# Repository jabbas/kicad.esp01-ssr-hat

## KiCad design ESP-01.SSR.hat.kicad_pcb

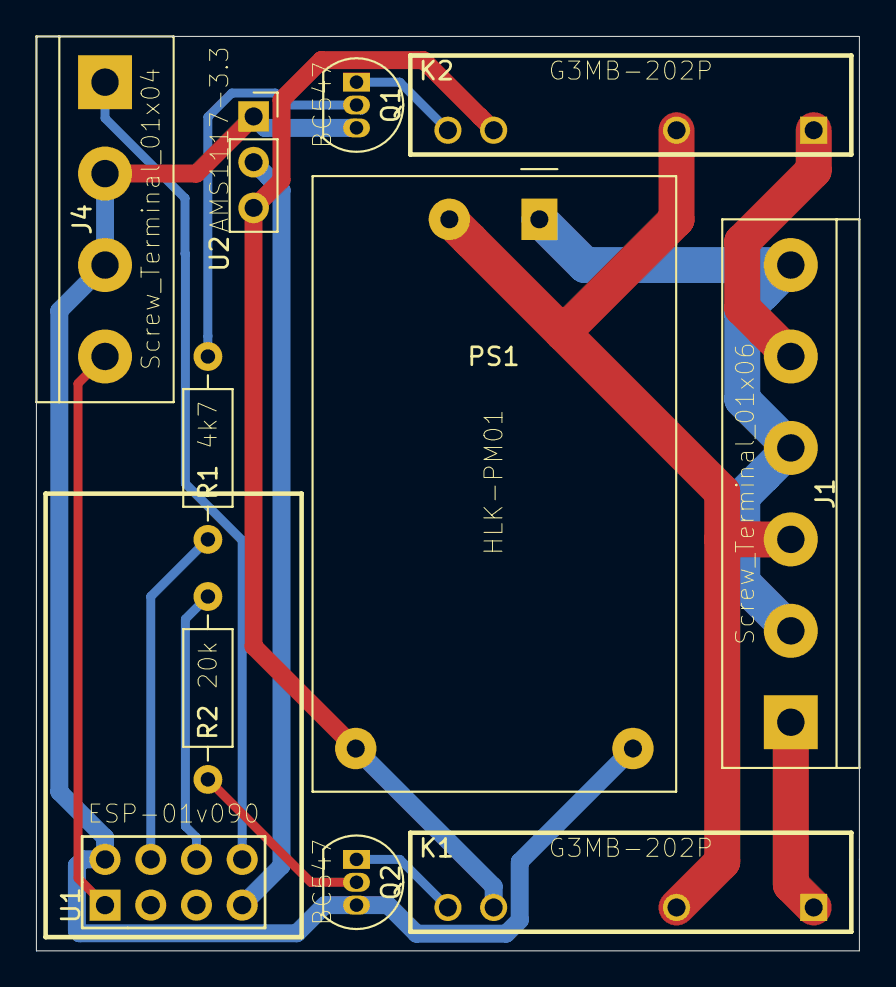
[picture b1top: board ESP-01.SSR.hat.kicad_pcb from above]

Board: 2 copper layers, 45.7 x 50.8 mm, 11 parts (0 on the bottom side), 15 nets.

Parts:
J1: Screw_Terminal_01x06; TerminalBlock_bornier-6_P5.08mm
J4: Screw_Terminal_01x04; TerminalBlock_bornier-4_P5.08mm
K1, K2: G3MB-202P; RELAY_G3MB-202P
PS1: HLK-PM01; Converter_ACDC_HiLink_HLK-PMxx
Q1, Q2: BC547; TO-92_Inline
R1: 4k7; R_Axial_DIN0207_L6.3mm_D2.5mm_P10.16mm_Horizontal
R2: 20k; R_Axial_DIN0207_L6.3mm_D2.5mm_P10.16mm_Horizontal
U1: ESP-01v090; ESP-01
U2: AMS1117-3.3; PinSocket_1x03_P2.54mm_Vertical

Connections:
+3.3V: U1.7, U2.2
+5V: K1.3, K2.3, PS1.4, U2.3
AC: J1.2, J1.4, J1.6, PS1.1
Earth: J1.3, K1.2, K2.2, PS1.2
GND: J4.2, J4.3, PS1.3, Q1.3, Q2.3, U1.2, U2.1
unnamed: J1.1, K1.1
unnamed: J1.5, K2.1
unnamed: J4.1, U1.8
unnamed: J4.4, U1.1
unnamed: K1.4, Q2.1
unnamed: K2.4, Q1.1
unnamed: Q1.2, R1.2
unnamed: Q2.2, R2.1
unnamed: R1.1, U1.4
unnamed: R2.2, U1.6

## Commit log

2019-09-10 beginning
2019-09-10 added transistors and pwr src
2019-09-10 prepared pcb
2019-09-11 updated wiring
2019-09-11 added tracks
2019-09-11 added tracks on pcb
2019-09-11 changed terminal blocks
2019-09-12 added edge cuts
2019-09-12 gerber output dir
2019-10-09 add resistor values
2019-10-21 board redesign
2019-10-21 add measurements
2019-10-22 shifted and moved elements
2019-11-20 final
